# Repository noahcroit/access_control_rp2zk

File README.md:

# Access Control Project
The project consists of <br>
- PCB design and the firmware of `Fail-Secure` door lock for the access control room. <br>
- Python worker of access control interface. This software will interract with the room management system later <br>

The project has 2 different version, v2023 and v2024.

## v2023 version
This version was focused on Proof-of-Concept and do a rapid prototype with both HW and SW. Micropython was used for the firmware development in RP2040 as for the Doorlock controller\
ZkTeco's access control was being used in this phase.

## v2024 version (the current ver.) 
PCB design with KiCAD for the doorlock controller. Hikvision's access control is being used in this phase instead of ZkTeco's.

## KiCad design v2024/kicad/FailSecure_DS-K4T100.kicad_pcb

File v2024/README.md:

# FailSecureDoor_RP2 version 2 (2024)
The room consists of slider automatic door which needs the fail-secure bolt-lock system when outage occured. <br>
KiCAD is used for the controller board design (in `kicad`) and RPi Pico C SDK framework is used for the firmware development (in `firmware`). <br>
By the dafault, each door has the access control device `DS-K1T105AM` installed alongside. <br>
Our access control software will used the Software Worker (in `worker`) to interface with `DS-K1T105AM` via `ISAPI` and fail-secure board via MQTT. <br>
<br>
### Hardware Diagram
 <br>
### Network Diagram
 <br>

### HW Installation
 <br>
 <br>
 <br>

### Worker
To build the image <br>
```
cd worker
docker build -t acworker2024-image .
```

To run the worker as container <br>
```
docker run --network host -d --restart always --name acworker acworker2024-image
```

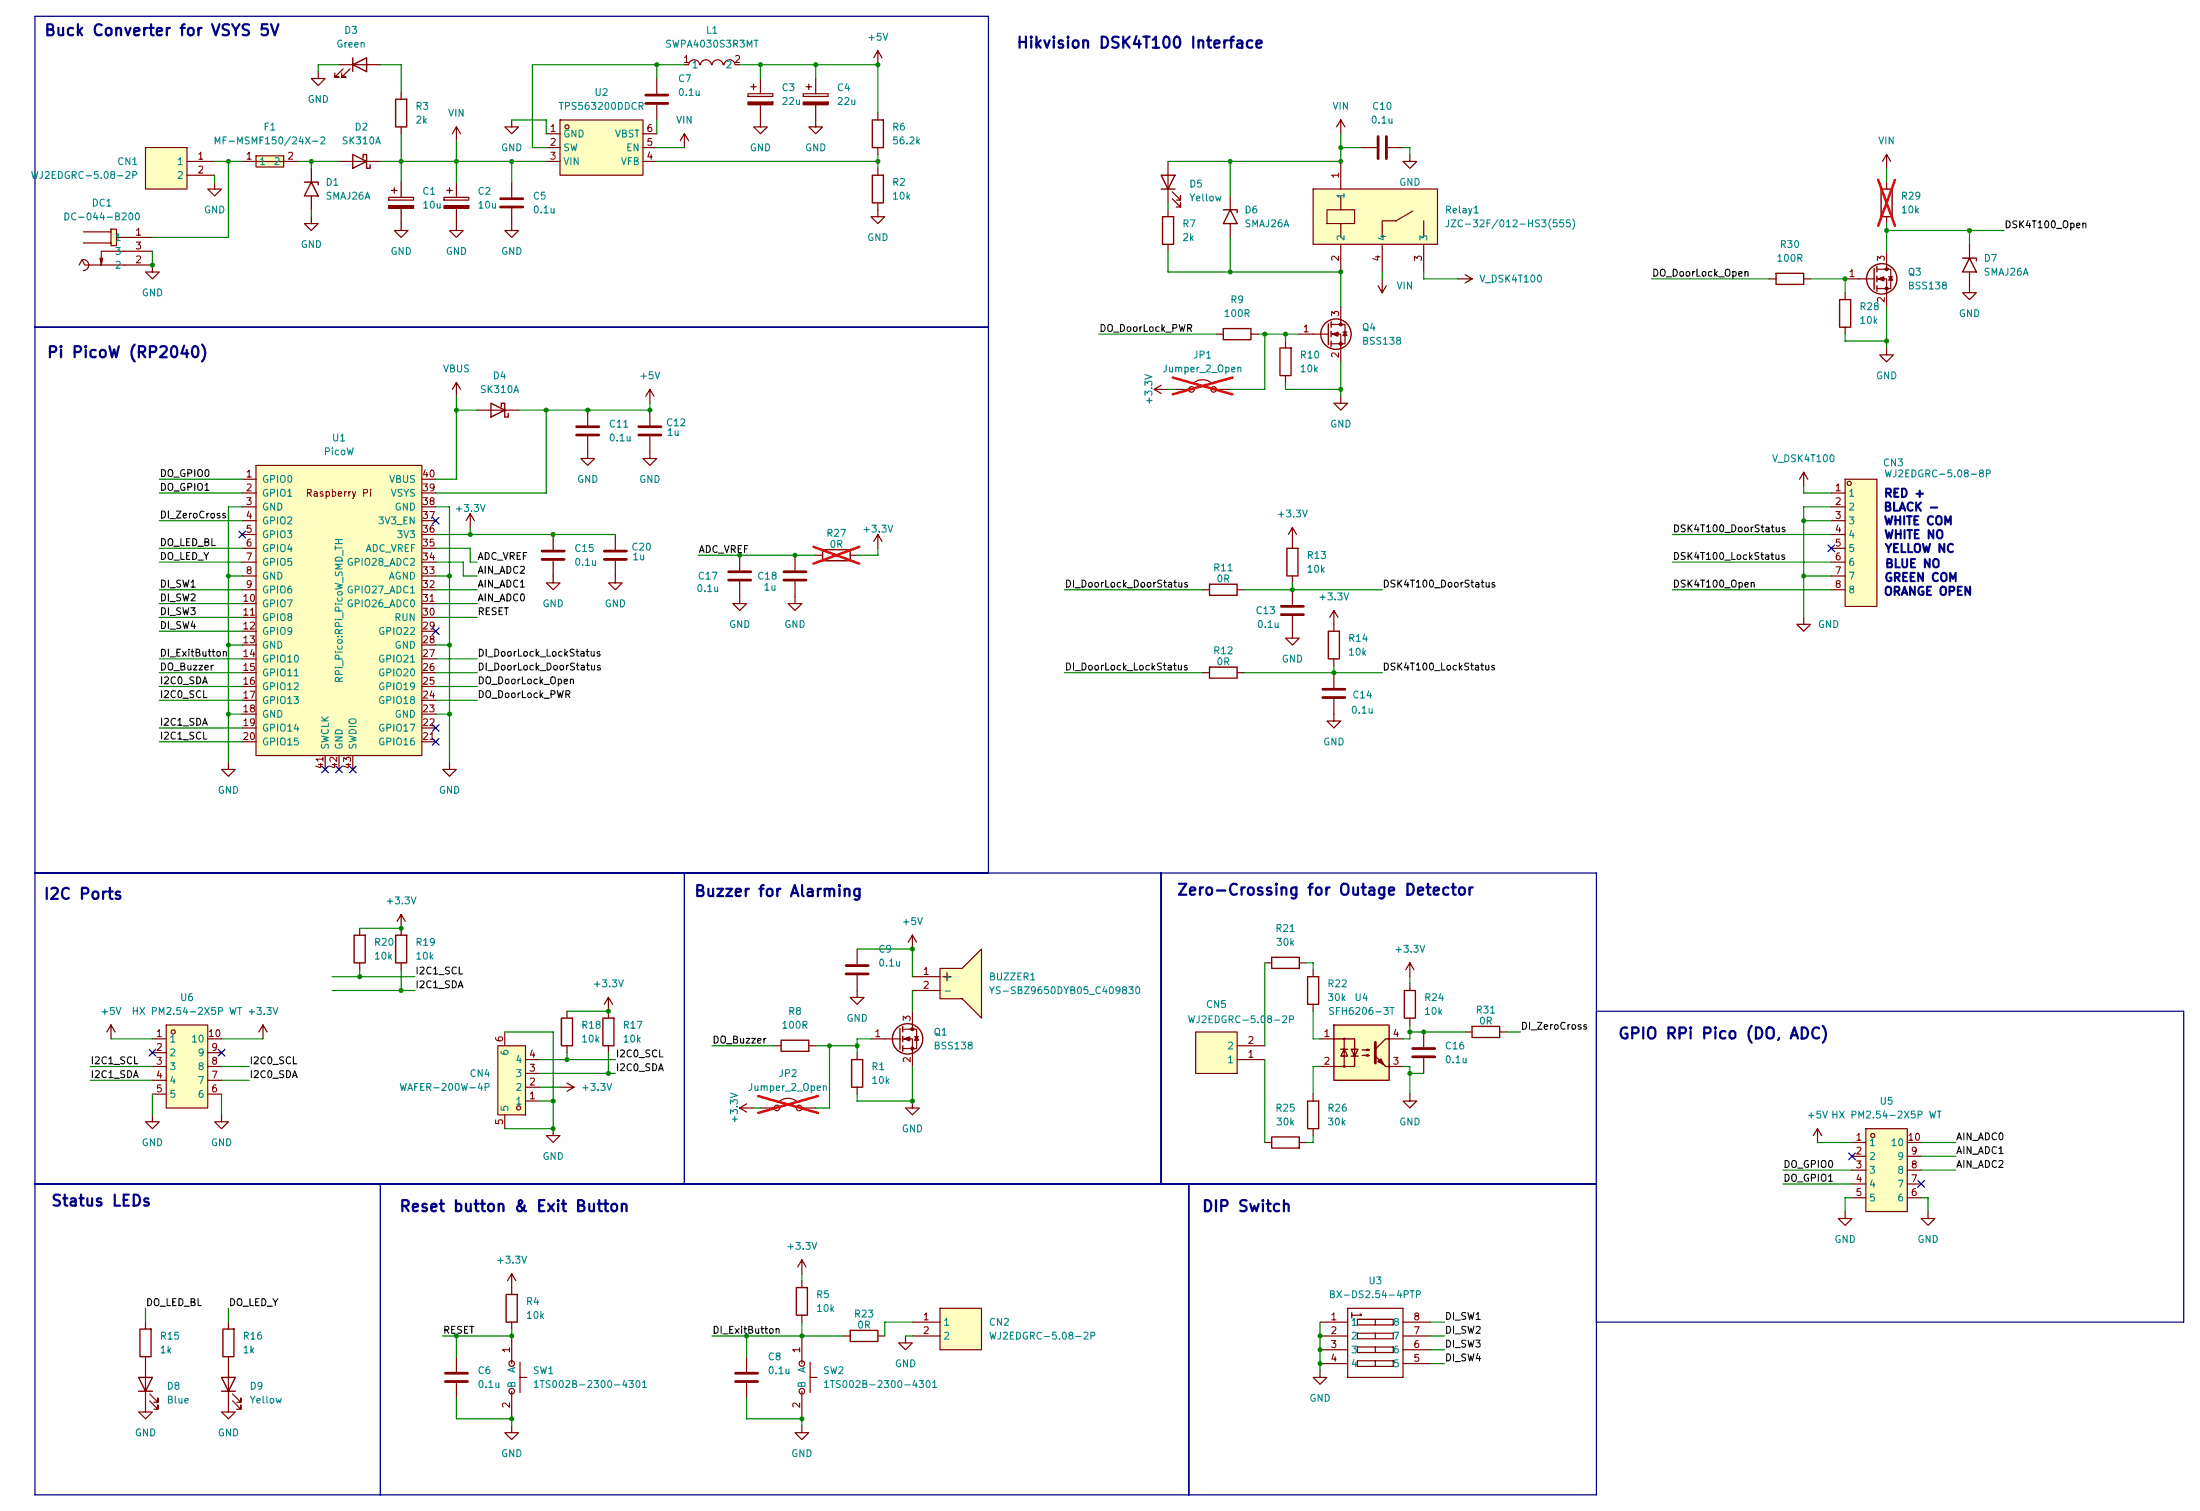
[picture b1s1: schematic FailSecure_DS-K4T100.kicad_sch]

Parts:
BUZZER1: YS-SBZ9650DYB05_C409830; BUZ-SMD_L9.6-W9.6-LS10.0-R; LCSC Part C409830
C1, C2: 10u; CP_Elec_4x5.4; LCSC Part C3343
C3, C4: 22u; CP_Elec_4x5.4; LCSC Part C3356
C5, C6, C7, C8, C9, C10, C11, C13, C14, C15, C16, C17: 0.1u; C_0805_2012Metric; Voltage 50V; Tolerance 100%; LCSC Part C138340
C12, C18, C20: 1u; C_1206_3216Metric; Voltage 50V; Tolerance 100%; LCSC Part C138340
CN1, CN2, CN5: WJ2EDGRC-5.08-2P; CONN-TH_2P-P5.08_WJ2EDGRC-5.08-2P; LCSC Part C3697
CN3: WJ2EDGRC-5.08-8P; CONN-TH_8P-P5.08_WJ2EDGRC-5.08-8P; LCSC Part C27587
CN4: WAFER-200W-4P; CONN-SMD_WAFER-200W-4P; LCSC Part C2840430
D1, D6, D7: SMAJ26A; D_SMA; LCSC Part C148225
D2, D4: SK310A; D_SMA; LCSC Part C91474
D3: Green; LED_0805_2012Metric; LCSC Part C2297
D5, D9: Yellow; LED_0805_2012Metric; LCSC Part C2296
D8: Blue; LED_0805_2012Metric; LCSC Part C2293
DC1: DC-044-B200; DC-IN-TH_DC-044-BXXX; LCSC Part C720573
F1: MF-MSMF150/24X-2; F1812; LCSC Part C78695
JP1, JP2: Jumper_2_Open; TestPoint_2Pads_Pitch2.54mm_Drill0.8mm; not fitted
L1: SWPA4030S3R3MT; IND-SMD_L4.0-W4.0_SMNR4012; LCSC Part C15269
Q1, Q3, Q4: BSS138; SOT-23-3; LCSC Part C431507
R1, R2, R4, R5, R10, R13, R14, R17, R18, R19, R20, R24, R28: 10k; R_0805_2012Metric; LCSC Part C17414
R3, R7: 2k; R_0805_2012Metric; LCSC Part C17604
R6: 56.2k; R_0805_2012Metric; LCSC Part C483186
R8, R9, R30: 100R; R_0805_2012Metric; LCSC Part C17408
R11, R12, R23, R31: 0R; R_0603_1608Metric; LCSC Part C21189
R15, R16: 1k; R_0805_2012Metric; LCSC Part C17513
R21, R22, R25, R26: 30k; R_1206_3216Metric; LCSC Part C17999
R27: 0R; R_0603_1608Metric; LCSC Part C304185; not fitted
R29: 10k; R_0805_2012Metric; LCSC Part C17414; not fitted
Relay1: JZC-32F/012-HS3(555); RELAY-TH_JZC-32F-012-HS3-555; LCSC Part C3632
SW1, SW2: 1TS002B-2300-4301; SW-SMD_L6.0-W3.5-LS8.0; LCSC Part C318833
U1: PicoW; RPi_PicoW_SMD_TH
U2: TPS563200DDCR; SOT-23-6_L2.9-W1.6-P0.95-LS2.8-BR; LCSC Part C97253
U3: BX-DS2.54-4PTP; SW-SMD_8P-L10.3-W6.2-P2.54-LS9.5-BL; LCSC Part C18078244
U4: SFH6206-3T; SMDIP-4_W9.53mm_Clearance8mm; LCSC Part C118295
U5, U6: HX PM2.54-2X5P WT; HDR-SMD_10P-P2.54-H-F-R2-C5-W8.5; LCSC Part C46635850

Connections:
+3.3V: C15.2, C20.1, CN4.2, JP1.1 (A), JP2.1 (A), R4.2, R5.2, R13.2, R14.2, R17.2, R18.2, R19.2, R20.2, R24.2, R27.1, U1.36 (3V3), U6.10
+5V: BUZZER1.1 (+), C3.1, C4.1, C9.1, C11.2, C12.1, D4.1 (K), L1.2, R6.2, U1.39 (VSYS), U5.1, U6.1
/ADC_VREF: C17.1, C18.1, R27.2, U1.35 (ADC_VREF)
/AIN_ADC0: U1.31 (GPIO26_ADC0), U5.10
/AIN_ADC1: U1.32 (GPIO27_ADC1), U5.9
/AIN_ADC2: U1.34 (GPIO28_ADC2), U5.8
/DI_DoorLock_DoorStatus: R11.2, U1.26 (GPIO20)
/DI_DoorLock_LockStatus: R12.2, U1.27 (GPIO21)
/DI_ExitButton: C8.1, R5.1, R23.2, SW2.1 (A), U1.14 (GPIO10)
/DI_SW1: U1.9 (GPIO6), U3.8
/DI_SW2: U1.10 (GPIO7), U3.7
/DI_SW3: U1.11 (GPIO8), U3.6
/DI_SW4: U1.12 (GPIO9), U3.5
/DI_ZeroCross: R31.1, U1.4 (GPIO2)
/DO_Buzzer: R8.1, U1.15 (GPIO11)
/DO_DoorLock_Open: R30.2, U1.25 (GPIO19)
/DO_DoorLock_PWR: R9.2, U1.24 (GPIO18)
/DO_GPIO0: U1.1 (GPIO0), U5.3
/DO_GPIO1: U1.2 (GPIO1), U5.4
/DO_LED_BL: R15.2, U1.6 (GPIO4)
/DO_LED_Y: R16.2, U1.7 (GPIO5)
/DSK4T100_DoorStatus: C13.2, CN3.4, R11.1, R13.1
/DSK4T100_LockStatus: C14.2, CN3.6, R12.1, R14.1
/DSK4T100_Open: CN3.8, D7.1 (A1), Q3.3 (D), R29.1
/I2C0_SCL: CN4.4, R18.1, U1.17 (GPIO13), U6.8
/I2C0_SDA: CN4.3, R17.1, U1.16 (GPIO12), U6.7
/I2C1_SCL: R20.1, U1.20 (GPIO15), U6.3
/I2C1_SDA: R19.1, U1.19 (GPIO14), U6.4
/RESET: C6.1, R4.1, SW1.1 (A), U1.30 (RUN)
GND: C1.2, C2.2, C3.2, C4.2, C5.1, C6.2, C8.2, C9.2, C10.2, C11.1, C12.2, C13.1, C14.1, C15.1, C16.1, C17.2, C18.2, C20.2, CN1.2, CN2.2, CN3.2, CN3.3, CN3.7, CN4.1, CN4.5, CN4.6, D1.2 (A2), D3.1 (K), D7.2 (A2), D8.1 (K), D9.1 (K), DC1.2, DC1.3, Q1.2 (S), Q3.2 (S), Q4.2 (S), R1.1, R2.1, R10.1, R28.1, SW1.2 (B), SW2.2 (B), U1.3 (GND), U1.8 (GND), U1.13 (GND), U1.18 (GND), U1.23 (GND), U1.28 (GND), U1.33 (AGND), U1.38 (GND), U2.1 (GND), U3.1, U3.2, U3.3, U3.4, U4.3, U5.5, U5.6, U6.5, U6.6
unnamed: BUZZER1.2 (-), Q1.3 (D)
unnamed: C16.2, R24.1, R31.2, U4.4
unnamed: CN1.1, DC1.1, F1.1
unnamed: CN2.1, R23.1
unnamed: CN5.1, R25.1
unnamed: CN5.2, R21.1
unnamed: D1.1 (A1), D2.2 (A), F1.2
unnamed: D3.2 (A), R3.2
unnamed: D5.1 (K), R7.2
unnamed: D6.2 (A2), Q4.3 (D), R7.1, Relay1.2
unnamed: D8.2 (A), R15.1
unnamed: D9.2 (A), R16.1
unnamed: JP1.2 (B), Q4.1 (G), R9.1, R10.2
unnamed: JP2.2 (B), Q1.1 (G), R1.2, R8.2
unnamed: Q3.1 (G), R28.2, R30.1
unnamed: R21.2, R22.1
unnamed: R22.2, U4.1
unnamed: R25.2, R26.1
unnamed: R26.2, U4.2
unnamed: C7.1, L1.1, U2.2 (SW)
unnamed: C7.2, U2.6 (VBST)
unnamed: R2.2, R6.1, U2.4 (VFB)
VBUS: D4.2 (A), U1.40 (VBUS)
VIN: C1.1, C2.1, C5.2, C10.1, D2.1 (K), D5.2 (A), D6.1 (A1), R3.1, R29.2, Relay1.1, Relay1.4, U2.3 (VIN), U2.5 (EN)
V_DSK4T100: CN3.1, Relay1.3

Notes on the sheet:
Zero-Crossing for Outage Detector
GPIO RPi Pico (DO, ADC)
Pi PicoW (RP2040)
GREEN COM
Status LEDs
BLACK -
WHITE NO
ORANGE OPEN
WHITE COM
Buzzer for Alarming
Reset button & Exit Button
RED +
DIP Switch
Buck Converter for VSYS 5V
BLUE NO
I2C Ports
Hikvision DSK4T100 Interface
YELLOW NC

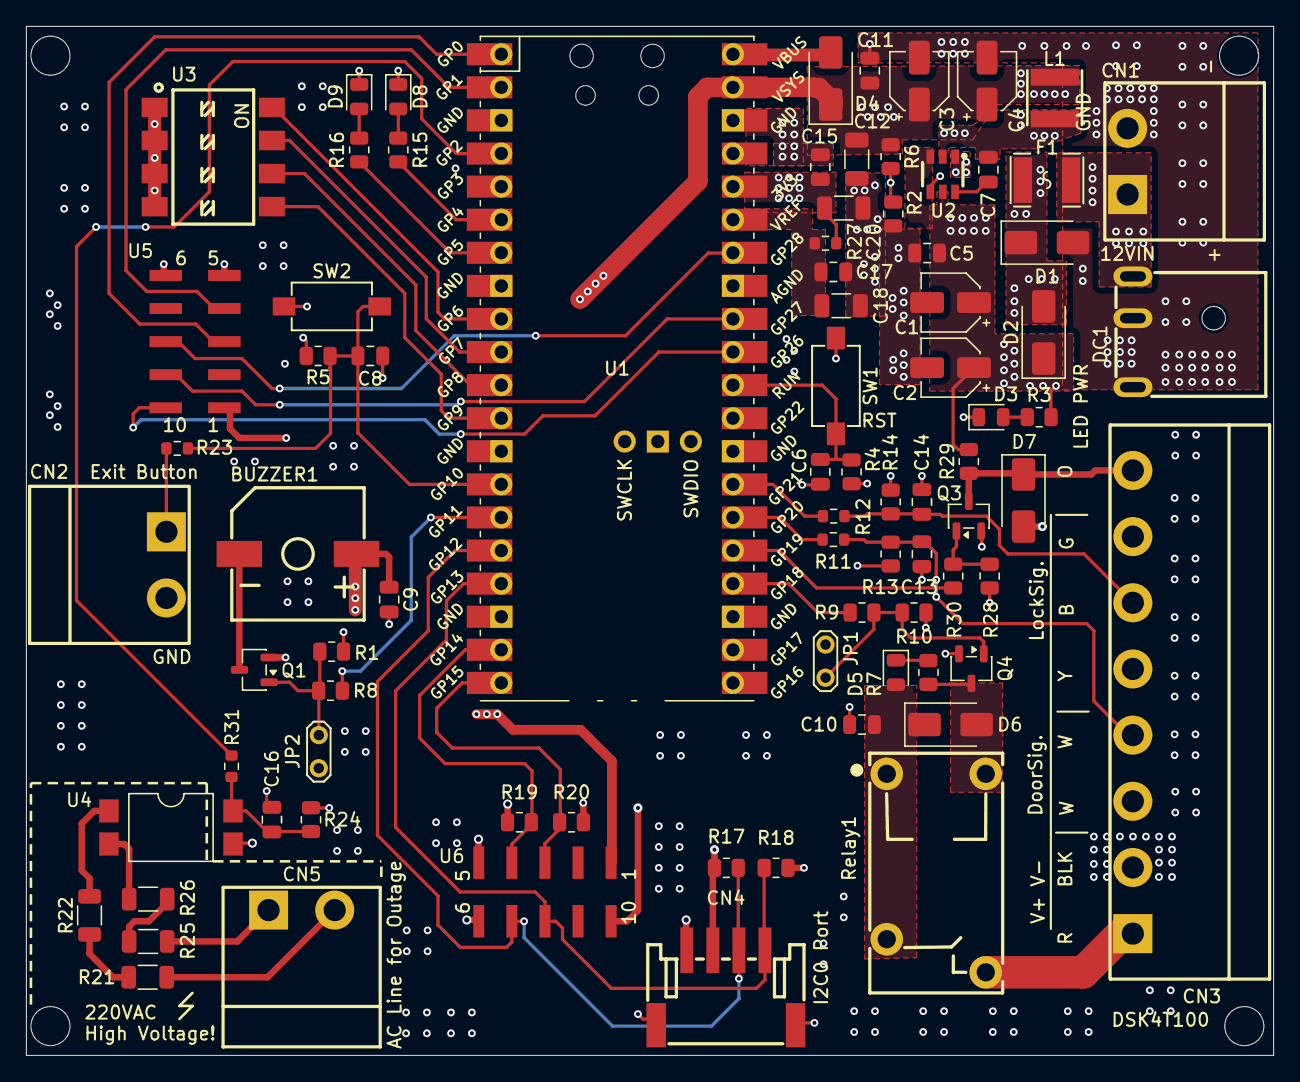
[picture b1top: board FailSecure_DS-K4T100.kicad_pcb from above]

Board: 4 copper layers, 95.8 x 79.0 mm, 82 parts (0 on the bottom side), 55 nets.

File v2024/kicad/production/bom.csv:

Designator,Footprint,Quantity,Value,LCSC Part #
BUZZER1,BUZ-SMD_L9.6-W9.6-LS10.0-R,1,YS-SBZ9650DYB05_C409830,C409830
"C1, C2",CP_Elec_4x5.4,2,10u,C3343
"C10, C11, C13, C14, C15, C16, C17, C5, C6, C7, C8, C9",0805,12,0.1u,C138340
"C12, C18, C20",1206,3,1u,C138340
"C3, C4",CP_Elec_4x5.4,2,22u,C3356
"CN1, CN2, CN5",CONN-TH_2P-P5.08_WJ2EDGRC-5.08-2P,3,WJ2EDGRC-5.08-2P,C3697
CN3,CONN-TH_8P-P5.08_WJ2EDGRC-5.08-8P,1,WJ2EDGRC-5.08-8P,C27587
CN4,CONN-SMD_WAFER-200W-4P,1,WAFER-200W-4P,C2840430
"D1, D6, D7",D_SMA,3,SMAJ26A,C148225
"D2, D4",D_SMA,2,SK310A,C91474
D3,0805,1,Green,C2297
"D5, D9",0805,2,Yellow,C2296
D8,0805,1,Blue,C2293
DC1,DC-IN-TH_DC-044-BXXX,1,DC-044-B200,C720573
F1,F1812,1,MF-MSMF150/24X-2,C78695
L1,IND-SMD_L4.0-W4.0_SMNR4012,1,SWPA4030S3R3MT,C15269
"Q1, Q3, Q4",SOT-23-3,3,BSS138,C431507
"R1, R10, R13, R14, R17, R18, R19, R2, R20, R24, R28, R4, R5",0805,13,10k,C17414
"R11, R12, R23, R31",0603,4,0R,C21189
"R15, R16",0805,2,1k,C17513
"R21, R22, R25, R26",1206,4,30k,C17999
"R3, R7",0805,2,2k,C17604
"R30, R8, R9",0805,3,100R,C17408
R6,0805,1,56.2k,C483186
RELAY1,RELAY-TH_JZC-32F-012-HS3-555,1,JZC-32F/012-HS3(555),C3632
"SW1, SW2",SW-SMD_L6.0-W3.5-LS8.0,2,1TS002B-2300-4301,C318833
U1,RPi_PicoW_SMD_TH,1,PicoW,
U2,SOT-23-6_L2.9-W1.6-P0.95-LS2.8-BR,1,TPS563200DDCR,C97253
U3,SW-SMD_8P-L10.3-W6.2-P2.54-LS9.5-BL,1,BX-DS2.54-4PTP,C18078244
U4,SMDIP-4_W9.53mm_Clearance8mm,1,SFH6206-3T,C118295
"U5, U6",HDR-SMD_10P-P2.54-H-F-R2-C5-W8.5,2,HX PM2.54-2X5P WT,C46635850

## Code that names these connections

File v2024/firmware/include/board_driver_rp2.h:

#ifndef BOARD_DRIVER_RP2_H
#define BOARD_DRIVER_RP2_H

#include <stdio.h>
#include "pico/stdlib.h"
#include "pico/cyw43_arch.h"
#include "hardware/pll.h"
#include "hardware/clocks.h"
#include "hardware/structs/pll.h"
#include "hardware/structs/clocks.h"
#include "hardware/watchdog.h"
#define DEBUG 1
#define TOTAL_NUM_GPIO_RP2 32
#define NUM_OF_MAX_TIMER_CB 16
#define WIFI_INIT_TIMEOUT 5

// serial print and sleep function
#if DEBUG == 1
#define driver_debug_print(x) printf(x)
#define driver_debug_print_int(x) printf("%d", x)
#define driver_debug_print_f32(x) printf("%f", x)
#else
#define driver_debug_print(x)
#define driver_debug_print_int(x)
#define driver_debug_print_float(x)
#endif

#define driver_sleep_ms(x) sleep_ms(x)

#define DI_ZEROCROSS 2
#define DI_EXITBUTTON 10
#define DI_SW1 6
#define DI_SW2 7
#define DI_SW3 8
#define DI_SW4 9
#define DO_LED_B 4
#define DO_LED_Y 5
#define DO_BUZZER 11
#define DO_DOORLOCK_PWR 18
#define DO_DOORLOCK_OPEN 19
#define DI_DOORSTATUS 20
#define DI_LOCKSTATUS 21
#define DO_ACCESSCTRLLOCK 28



void driver_rp2_sysinit();
void driver_rp2_set_gpio_input(uint8_t gpio_num, bool use_interrupt);
void driver_rp2_set_gpio_output(uint8_t gpio_num);
bool driver_rp2_read_gpio(uint8_t gpio_num);
void driver_rp2_write_gpio(uint8_t gpio_num, bool value);
void driver_rp2_enable_gpio_global_interrupt();
void driver_rp2_set_gpio_callback(uint8_t gpio_num, void (*cb) (void));
void driver_rp2_create_global_tick(uint32_t tick_period_ms);
uint32_t driver_rp2_get_global_tick();
int driver_rp2_enable_wifi();
int driver_rp2_connect_to_wifi(const char *ssid, const char *pwd, uint32_t timeout);
bool driver_rp2_is_wifi_connected();
void driver_rp2_watchdog_enable(uint32_t delay_ms);
void driver_rp2_watchdog_feed();

#endif

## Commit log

2024-01-29 add draft design diagrams
2024-01-29 real hardware image
2024-01-29 add rp2 codes
2024-02-02 rp2, add scheduler
2024-02-02 rp2, update main and secure_doorlock
2024-02-02 move rp2's sources to rp2 folder
2024-02-03 rp2, add more comment on how to use scheduler
2024-02-03 rp2, activate exit button even in IDLE state
2024-02-03 rp2, add MQTT to main
2024-02-03 rp2, add .json file for default network config
2024-02-03 rp2, add buzzer for alarm when outage is occured
2024-02-03 worker, add door worker
2024-02-08 worker, update all files
2024-02-08 rp2, convert data into str before pack the MQTT message
2024-02-08 worker, update
2024-02-08 worker, add REDIS authentication
2024-02-09 rp2, add lastwill before go to ACTIVE state when outage occur + buzzer fadeout
2024-02-09 worker, adjust asyncio.sleep duration
2024-02-12 rm old worker, test aiomqtt and update config.json
2024-02-12 remove unwanted cache folder
2024-02-19 wworker, update access_control class
2024-02-19 worker, update worker for a new access ctrl class
2024-02-19 worker, update tag in config file
2024-02-19 add test GUI for worker, created by using QT
2024-02-20 worker, add lock unlock function
2024-02-20 worker, add lock/unlock tag to config.json
2024-02-20 worker, wrong spell for epoch
2024-02-20 worker, change reserve function to hold the door after start time
2024-02-21 add pyzk examples
2024-02-21 worker, start to listen attendance with pyzk livecapture
2024-02-22 worker, update zk attendance capture task
2024-02-22 worker, update zk attendance live capture
2024-02-22 fix previous atten livecapture
2024-03-10 update testapp
2024-03-10 add REDIS API instruction for worker
2024-03-15 update requirement.txt for worker
2024-03-15 add Dockerfile to deploy worker
2024-03-15 fix name of requirements.txt
2024-03-17 remove pyzk=0.9.1 out from requirements.txt (choose to install manually)
2024-03-20 update Dockerfile for deploy worker
2024-03-21 Update Dockerfile
2024-03-21 Update README, add worker deployment instruction
2024-03-21 worker, use logging.info() instead of print()
2025-01-23 create v2023 and start a new version (v2024)
2025-01-23 update folder struct
2025-01-25 update README for a new project structure
2025-01-26 add ver2024, start with example code for rp2
2025-02-26 add firmware folder for rp2 failsecure controller
2025-02-26 update files in firmware
2025-03-10 firmware, add app button
2025-03-10 firmware, add app LED
2025-03-10 firmware, add app buzzer
2025-03-10 firmware, add driver layer for rp2040
2025-03-10 firmware, update main and CMakefile
2025-03-11 firmware, add app for boltlock dsk4t100
2025-03-11 update firmware
2025-03-11 firmware, fix GPIO interrupt bug from NULL fn pointer
2025-03-11 firmware, update main
2025-03-11 fw, rename app_m202g to app_accessctrl
2025-03-12 firmware, add app_accessctrl
2025-03-12 firmware, update driver
2025-03-12 firmware, update all for fw v0.1 (without MQTT yet)
2025-03-17 firmware, update rp2 driver by adding WiFi and WDT
2025-03-17 firmware, update main for FW=v0.2 (MQTT added)
2025-03-17 firmware, add app_mqtt.h
2025-03-17 start to add worker code
2025-03-19 add ISAPI person management example
2025-03-19 update worker
2025-03-19 update ISAPI examples
2025-03-22 update ISAPI example, auth, person managements
2025-03-22 ISAPI example, add config.json and user.json for examples
2025-03-22 ISAPI, add update user and valid time function
2025-03-22 ISAPI example, create user folder and move user.json to it
2025-03-23 ISAPI example, add Remote Door Control
2025-03-24 worker : update access control worker
2025-03-24 worker : replace config.json of worker with the new default one
2025-03-26 ISAPI, add event example
2025-03-26 update worker for event
2025-03-29 update worker, remove callback function for event listening and move to door class
2025-03-29 firmware, add lock/unlock pin and change release process
2025-03-29 firmware, update app_accessctrl for exit button in slidedoor
2025-03-30 firmware, fix the reversed logic of door status
2025-03-31 worker, add islocked tag for door monitoring and update unlock_scheduler
2025-03-31 worker update
2025-03-31 update event example
2025-04-03 ISAPI example, add message decoding state machine to event_example
2025-04-10 update worker. but still cannot solve the SSL cer problem
2025-04-11 worker, add Dockerfle
2025-04-11 add Docker build process for worker in README.md
2025-04-18 add pictures of v2024 in etc folder
2025-04-18 add KiCAD pcb files of v2024
2025-04-18 update READMEs
2025-05-21 Fix wrong timezone in docker container of worker
2025-11-09 Kicad, add a new parts from JLCPCB
2025-11-09 Kicad, update schematic for access control v2025
2025-11-09 Kicad, update PCB layout for a new schematic
2025-11-10 Kicad, move 2x5 connector to fit inside the board
2025-11-10 update PCB silkscreen
2025-11-10 Kicad, add LCSC part number to forgotten devices & Don't populate jumper
2025-11-10 Update BOM by remove extended part as much as posible
2026-01-29 FW, update I/O for v2025 board
2026-02-07 move the FW for only-boltlock door, set to lock as power-on state
2026-02-07 fw, do not try to unlock in the idle state (let AC do the locking) + disable WIFI
2026-02-16 update fw
2026-02-16 add schematic v2 as PDF file
2026-02-16 add PCB productioni file
2026-02-23 worker, change from print() to logger.info() for logging
2026-02-23 fw, fix exit button to hold unlock until released the button
2026-03-15 add ngrok setup script
2026-04-05 disble WLAN temporally
2026-04-05 add auto-authen installation
